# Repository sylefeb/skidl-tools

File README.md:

# skidl-tools

## TL;DR

This tool helps doing iterative design between a PCB described in [skidl](https://devbisme.github.io/skidl/)
(python code) and [KiCad](https://www.kicad.org/)'s PCB editor (PcbNew): start placing and routing, go
back to code and add components, resume editing without loosing your previous changes.

**Note:** (thanks to TheZoq2 for pointing this out) In many cases you do not need this
tool and can simply use `generate_netlist()` from skidl and use KiCad's `Import > Netlist`
feature to merge changes with your current PCB design. Best to try that first as KiCad provides
multiple options in dealing with conflicts.

## What is in this repo?

A collection of tools (one for now!) to help with PCB design using [KiCad](https://www.kicad.org/)
and [skidl](https://devbisme.github.io/skidl/).

The main tool is `skidl-updater`, it takes a previous design and a newly generated
PCB from skidl, and remaps prior edits onto the new file. See [Example workflow](#example-workflow) below.

**This is very much work in progress**, please see [Limitations](#limitations).

## How to compile

```
git submodule init
git submodule update
mkdir BUILD
cd BUILD
cmake ../updater/
make install
```

## Example workflow

This tutorial example walks through the process of progressively adding components to a board, using `skidl-updater` at each step to import prior changes to the PCB. For the sake of the tutorial the example is voluntarily cut
into many small incremental steps.

> Note: the tutorial assumes some familiarity with KiCad's layout editor (PcbNew).

> This tutorial uses KiCad 7.

The goal is to design a simple 'half-PMOD' (using only one PMOD row)
with four LEDs on it. All files are in [`examples/pmod_leds`](examples/pmod_leds).
Here is the workflow:
- We start by a simple script defining VCC and GND nets and adding a connector, [board1.py](examples/pmod_leds/board1.py). Note how the connector is using a `ref` attribute (`PMOD`), this is essential to the inner workings of `skidl-updater`: each component has to have a unique `ref`.
To generate the board we run `python board1.py`.

> Note: the script has to be run from a special python environment provided by KiCad, please refer to skidl's documentation.

- We open the generated [board1.kicad_pcb](examples/pmod_leds/board1.kicad_pcb), create a board contour and place the connector, save the board and exit.

- Now, we add the LEDs in [board2.py](examples/pmod_leds/board2.py). We generate [board2.kicad_pcb](examples/pmod_leds/board2.kicad_pcb) by running `python board2.py`.
However `board2.kicad_pcb` has lost the contour and placement of the connector  we did at step one. We don't want to redo what we just did, so we use `skidl-updater`:

`skidl-updater -p board1.kicad_pcb -n board2.kicad_pcb -o board2_edit.kicad_pcb`

- This command takes the content of `board1.kicad_pcb` as reference and imports it into `board2.kicad_pcb` to obtain `board2_edit.kicad_pcb`. We now can open `board2_edit.kicad_pcb` and are ready to place the LEDs, prior edits have been imported! We now place the LEDs neatly on the board, save and exit.

- We also need a resistor per LED, so we add them to obtain [board3.py](examples/pmod_leds/board3.py) and
run  `python board3.py` to obtain `board3.kicad_pcb`, which has again lost all our edits. `skidl-updater` to the rescue!

`skidl-updater -p board2_edit.kicad_pcb -n board3.kicad_pcb -o board3_edit.kicad_pcb`

- Final step, we need to connect everything together. Each LED will be lit by one of the four signals from the half-PMOD. We add the connections to obtain [board4.py](examples/pmod_leds/board4.py) and generate the PCB with
`python board4.py`. Again all changes are lost, and we use `skidl-updater` to save the day:

`skidl-updater -p board3_edit.kicad_pcb -n board4.kicad_pcb -o board4_edit.kicad_pcb`

The board is done! (maybe don't fab it, it's just a quick example ;) ).

> Note: In the example we save each step, but of course you can start from the
> same file, running `skidl-updater -p board_edit.kicad_pcb -n board.kicad_pcb -o board_edit.kicad_pcb`
> works (it will rename the previous file as a `.bak`, in case something goes wrong).

## Limitations

**There are potential 'gotchas', be worried if kicad reports a warning when opening
the PCB file.**

**Use at your own risks -- always double check your design and the nets.**

Some known issues and workarounds:

- **Removing a component**. The tool is geared towards the idea of progressively
*adding* components to the board. When removing a component, that is the script
no longer produce a component of a given `ref`, then edit the previous version
 `.kicad_pcb` and also delete the component from the board. Otherwise, the
 updater will keep bringing it back, introducing various problems with nets.

- **Swapping the footprint of a component**. As with *Removing a component*,
make sure to edit the previous version `.kicad_pcb` and delete the component
first. You will have to place the new footprint again, but that guarantees the
footprint is properly updated.

> Found another limitation? Please fill-in an issue in github.

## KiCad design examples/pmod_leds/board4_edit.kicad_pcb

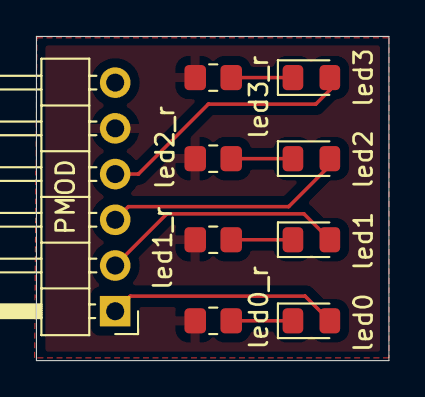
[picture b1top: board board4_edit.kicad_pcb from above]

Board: 2 copper layers, 19.6 x 18.0 mm, 9 parts (0 on the bottom side), 9 nets.

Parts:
PMOD: Conn_01x06; PinHeader_1x06_P2.54mm_Horizontal
led0, led1, led2, led3: LED; LED_0805_2012Metric_Pad1.15x1.40mm_HandSolder
led0_r, led1_r, led2_r, led3_r: 270; R_0805_2012Metric_Pad1.20x1.40mm_HandSolder

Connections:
GND: PMOD.5, led0_r.1, led1_r.1, led2_r.1, led3_r.1
unnamed: led0.1, led0_r.2
unnamed: PMOD.1, led0.2
unnamed: led1.1, led1_r.2
unnamed: PMOD.2, led1.2
unnamed: led2.1, led2_r.2
unnamed: PMOD.3, led2.2
unnamed: led3.1, led3_r.2
unnamed: PMOD.4, led3.2

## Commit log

2024-09-11 module url change
2024-09-11 git attributes
2024-09-16 footprint replacement as opposed to more subtle attribute tweaking
2024-09-16 proper transfer of nets
2024-09-17 command line args
2024-09-18 cleanup
2024-09-18 minor fix
2024-10-09 improved net transfer
2024-10-13 warning on missing pad
2024-10-16 supporting multiple pads with same name
2024-10-21 documenting
2024-10-21 typo, license
2024-10-22 license, documenting
2024-10-22 added note on Import-Netlist
2025-05-21 feat: ability to selectively update footprints (regexp on command line) instead of always preserving existing ones
